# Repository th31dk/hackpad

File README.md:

# the_idk's Hackpad
This is my submission for hackpad.

## BOM
[BOM File](https://github.com/th31dk/hackpad/blob/main/Hackpad%20PCB/BOM.csv)  
9 Cherry MX Switches  
9 1N4148 Diodes  
9 Blank DSA Keycaps  
16 SK6812 MINI-E LEDs  
1 EC11 Rotary Encoder  
1 XIAO RP2040  
1 0.91in OLED Display
4 M3x16 Bolt  
4 M3 Heatset

## CAD
|Bottom|Top|
|---|---|
|||

Assembly:  
  
It's help together by 4 heat inserts and 4 M3x16 bolts.

## PCB
|Schematic|PCB|
|---|---
|||

PCB 3D Model:  
  
This was my first time using KiCad, so it isn't the best. Although it took the longest out of everything in this project, I had a lot of fun designing the PCB.

## Final Thoughts
Overall, I learned a lot from this project. In the future, I'm going to try to make a better revision.

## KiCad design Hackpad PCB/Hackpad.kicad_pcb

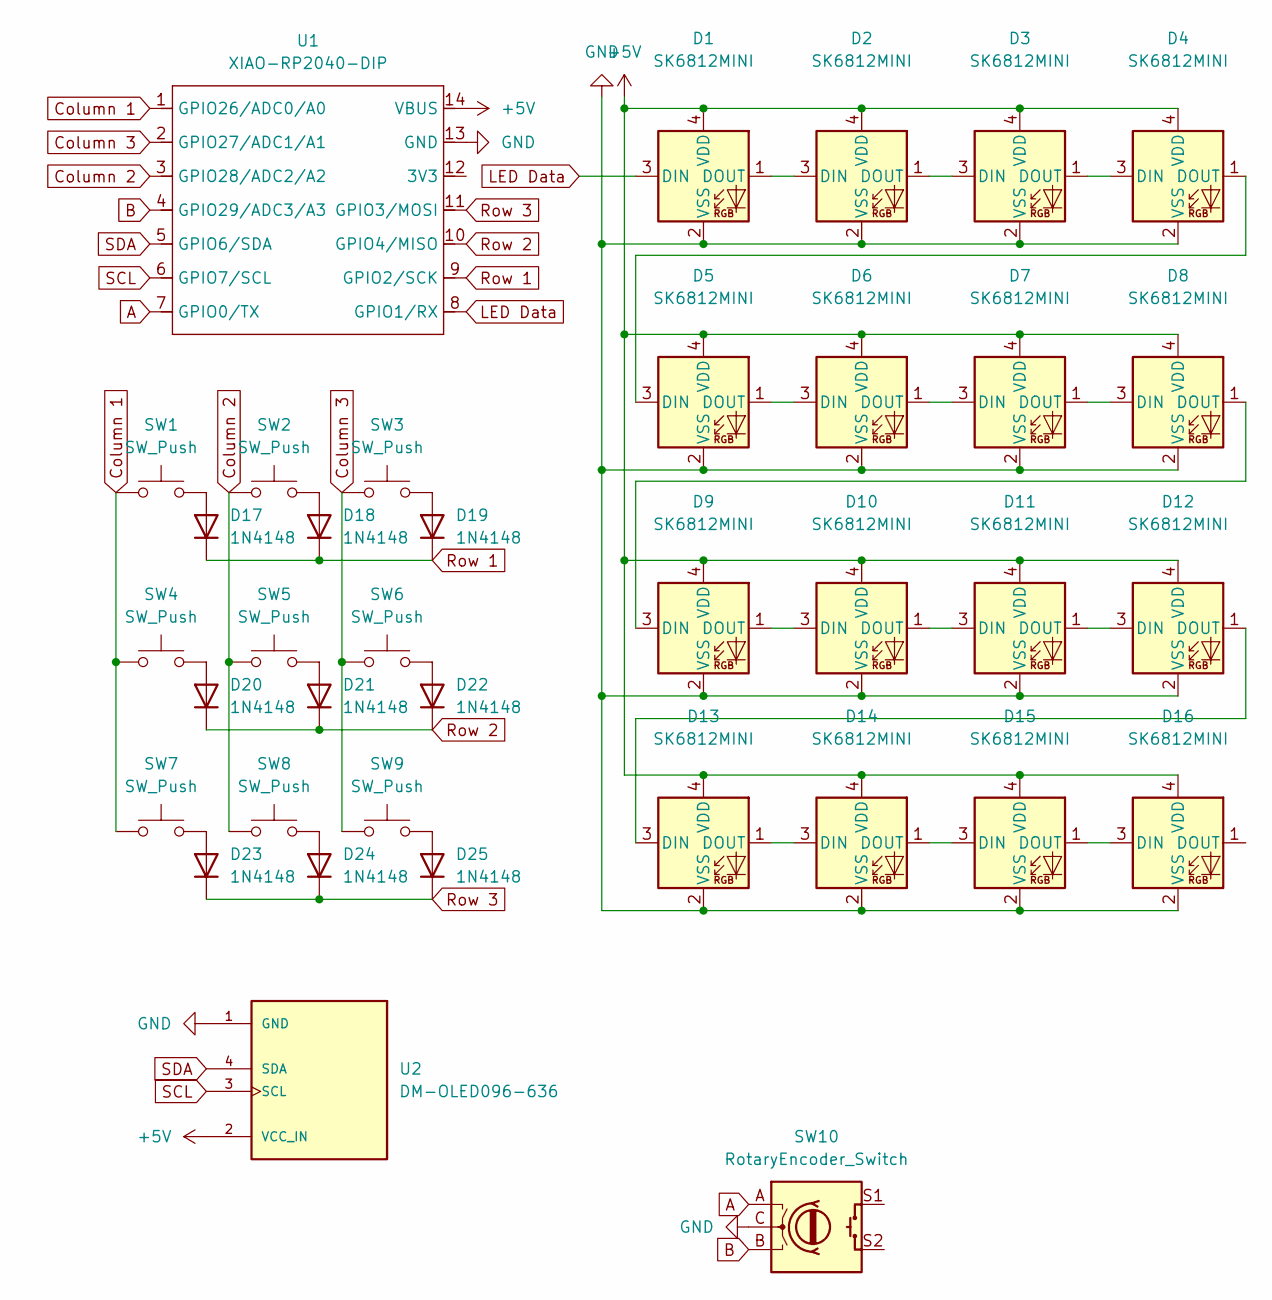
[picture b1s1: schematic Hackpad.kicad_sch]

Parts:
D1, D2, D3, D4, D5, D6, D7, D8, D9, D10, D11, D12, D13, D14, D15, D16: SK6812MINI; LED_SK6812MINI_PLCC4_3.5x3.5mm_P1.75mm
D17, D18, D19, D20, D21, D22, D23, D24, D25: 1N4148; D_DO-35_SOD27_P7.62mm_Horizontal
SW1, SW2, SW3, SW4, SW5, SW6, SW7, SW8, SW9: SW_Push; SW_Cherry_MX_1.00u_PCB
SW10: RotaryEncoder_Switch
U1: XIAO-RP2040-DIP
U2: DM-OLED096-636; SSD1306-0.91-OLED-4pin-128x32; PARTREV 2018-09-10

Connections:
+5V: D1.4 (VDD), D2.4 (VDD), D3.4 (VDD), D4.4 (VDD), D5.4 (VDD), D6.4 (VDD), D7.4 (VDD), D8.4 (VDD), D9.4 (VDD), D10.4 (VDD), D11.4 (VDD), D12.4 (VDD), D13.4 (VDD), D14.4 (VDD), D15.4 (VDD), D16.4 (VDD), U1.14 (VBUS), U2.2 (VCC_IN)
A: SW10.A, U1.7 (GPIO0/TX); also elsewhere on the board
B: SW10.B, U1.4 (GPIO29/ADC3/A3); also elsewhere on the board
Column 1: SW1.1, SW4.1, SW7.1, U1.1 (GPIO26/ADC0/A0)
Column 2: SW2.1, SW5.1, SW8.1, U1.3 (GPIO28/ADC2/A2)
Column 3: SW3.1, SW6.1, SW9.1, U1.2 (GPIO27/ADC1/A1)
GND: D1.2 (VSS), D2.2 (VSS), D3.2 (VSS), D4.2 (VSS), D5.2 (VSS), D6.2 (VSS), D7.2 (VSS), D8.2 (VSS), D9.2 (VSS), D10.2 (VSS), D11.2 (VSS), D12.2 (VSS), D13.2 (VSS), D14.2 (VSS), D15.2 (VSS), D16.2 (VSS), SW10.C, U1.13 (GND), U2.1 (GND); also elsewhere on the board
LED Data: D1.3 (DIN), U1.8 (GPIO1/RX)
unnamed: D1.1 (DOUT), D2.3 (DIN)
unnamed: D2.1 (DOUT), D3.3 (DIN)
unnamed: D3.1 (DOUT), D4.3 (DIN)
unnamed: D4.1 (DOUT), D5.3 (DIN)
unnamed: D5.1 (DOUT), D6.3 (DIN)
unnamed: D6.1 (DOUT), D7.3 (DIN)
unnamed: D7.1 (DOUT), D8.3 (DIN)
unnamed: D8.1 (DOUT), D9.3 (DIN)
unnamed: D9.1 (DOUT), D10.3 (DIN)
unnamed: D10.1 (DOUT), D11.3 (DIN)
unnamed: D11.1 (DOUT), D12.3 (DIN)
unnamed: D12.1 (DOUT), D13.3 (DIN)
unnamed: D13.1 (DOUT), D14.3 (DIN)
unnamed: D14.1 (DOUT), D15.3 (DIN)
unnamed: D15.1 (DOUT), D16.3 (DIN)
unnamed: D17.2 (A), SW1.2
unnamed: D18.2 (A), SW2.2
unnamed: D19.2 (A), SW3.2
unnamed: D20.2 (A), SW4.2
unnamed: D21.2 (A), SW5.2
unnamed: D22.2 (A), SW6.2
unnamed: D23.2 (A), SW7.2
unnamed: D24.2 (A), SW8.2
unnamed: D25.2 (A), SW9.2
Row 1: D17.1 (K), D18.1 (K), D19.1 (K), U1.9 (GPIO2/SCK)
Row 2: D20.1 (K), D21.1 (K), D22.1 (K), U1.10 (GPIO4/MISO)
Row 3: D23.1 (K), D24.1 (K), D25.1 (K), U1.11 (GPIO3/MOSI)
SCL: U1.6 (GPIO7/SCL), U2.3 (SCL)
SDA: U1.5 (GPIO6/SDA), U2.4 (SDA)

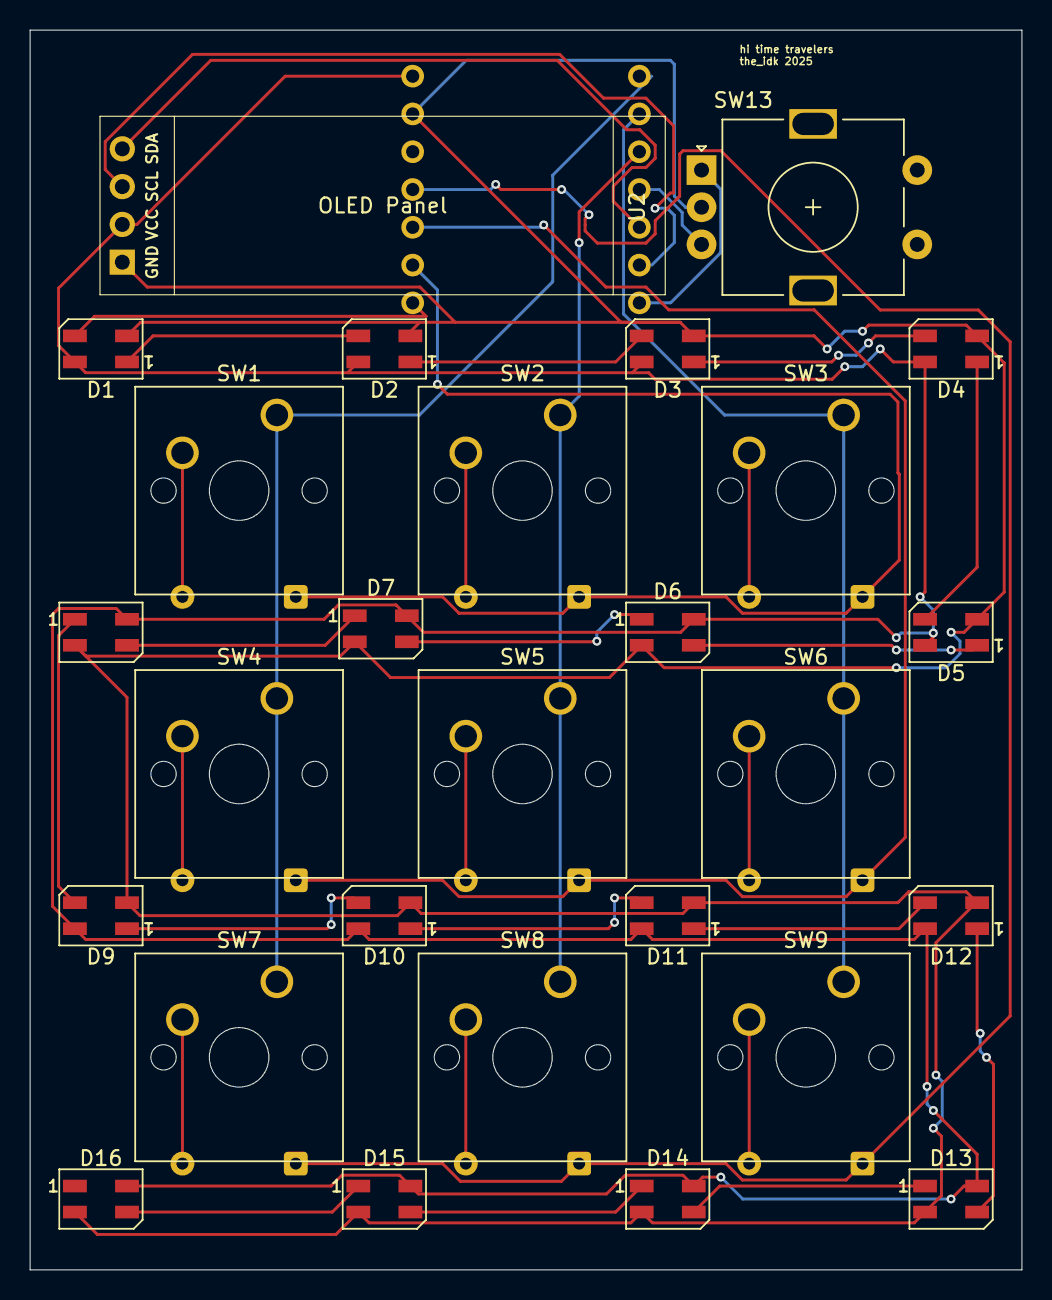
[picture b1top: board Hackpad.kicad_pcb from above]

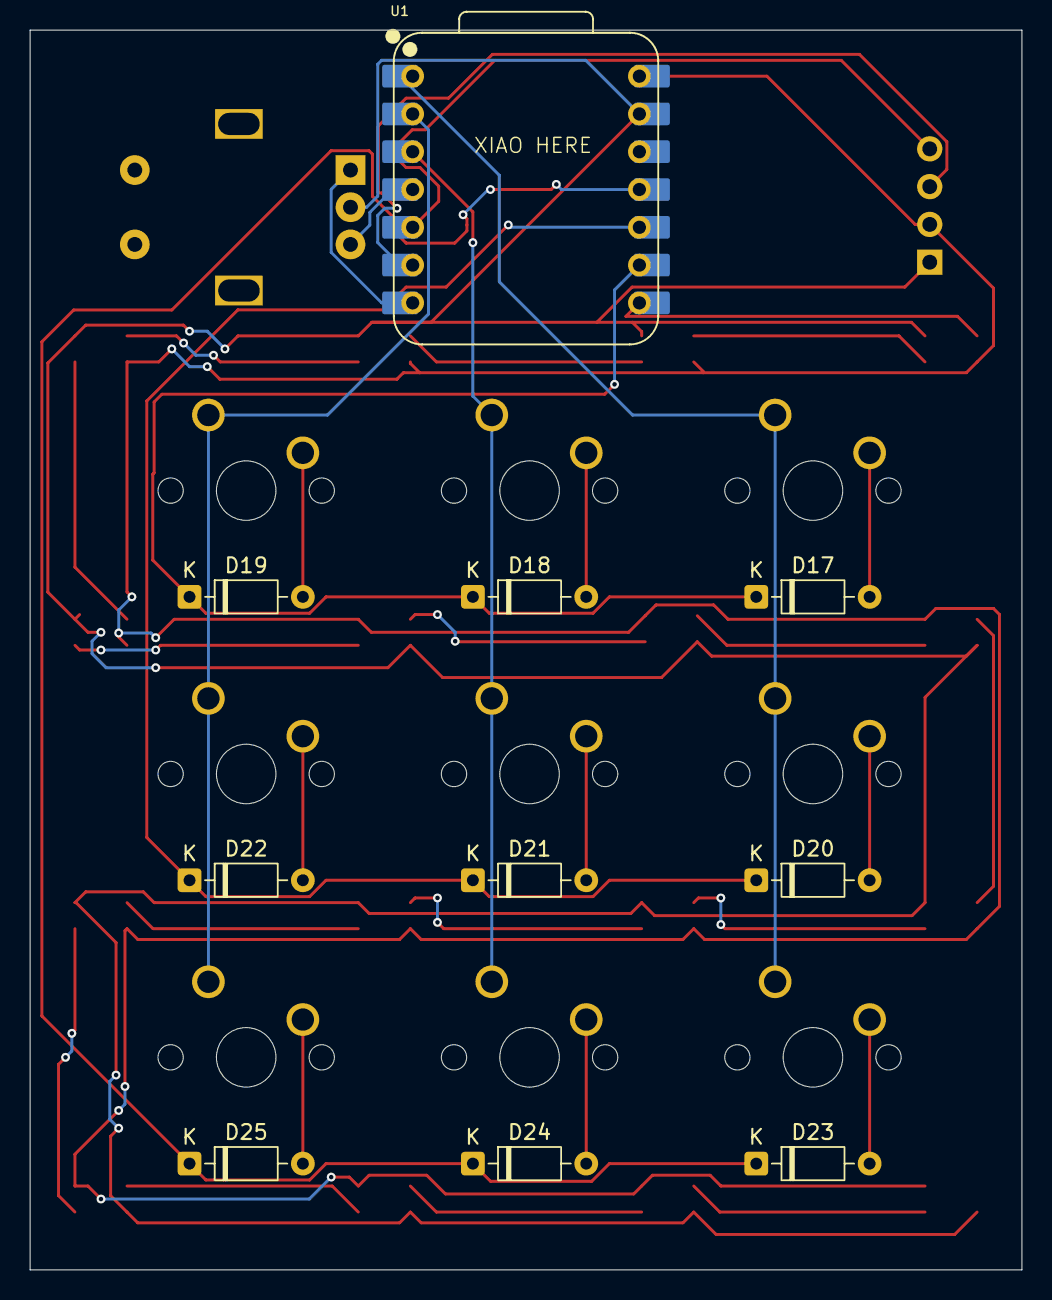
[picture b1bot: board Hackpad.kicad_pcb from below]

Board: 2 copper layers, 66.7 x 83.3 mm, 37 parts (10 on the bottom side), 37 nets.

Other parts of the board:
SW13: RotaryEncoder; RotaryEncoder_Alps_EC11E-Switch_Vertical_H20mm

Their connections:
A: SW13.A; also elsewhere on the board
B: SW13.B; also elsewhere on the board
GND: SW13.C; also elsewhere on the board

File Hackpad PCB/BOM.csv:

"Reference","Qty","Value","DNP","Exclude from BOM","Exclude from Board","Footprint","Datasheet"
"D1,D2,D3,D4,D5,D6,D7,D8,D9,D10,D11,D12,D13,D14,D15,D16","16","SK6812MINI","","","","LED_SMD:LED_SK6812MINI_PLCC4_3.5x3.5mm_P1.75mm","https://cdn-shop.adafruit.com/product-files/2686/SK6812MINI_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"
"D17,D18,D19,D20,D21,D22,D23,D24,D25","9","1N4148","","","","Diode_THT:D_DO-35_SOD27_P7.62mm_Horizontal","https://assets.nexperia.com/documents/data-sheet/1N4148_1N4448.pdf"
"SW1,SW2,SW3,SW4,SW5,SW6,SW7,SW8,SW9","9","SW_Push","","","","Button_Switch_Keyboard:SW_Cherry_MX_1.00u_PCB","~"
"SW13","1","RotaryEncoder_Switch","","","","","~"
"U1","1","XIAO-RP2040-DIP","","","","OPL:XIAO-RP2040-DIP",""
"U2","1","DM-OLED096-636","","","","OLED:SSD1306-0.91-OLED-4pin-128x32",""

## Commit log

2025-12-01 Add README
2025-12-02 Add BOM
2025-12-02 updated repo
2025-12-02 README
